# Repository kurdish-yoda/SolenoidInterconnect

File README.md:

# SENSA - Solenoid Interconnect

Genral repository for files pertaining solidnoid interconnect board that is part of SENSA GROUP.  

## Description
The PCB accepts signals comming from 8 solenoids at once and outputs them at individual pinouts. It acts as a "break" in the cable where it also further outputs all of the inputs. ]

## Features
- Daisy chainable.
- 8 solenoid outputs. 

## Pictures

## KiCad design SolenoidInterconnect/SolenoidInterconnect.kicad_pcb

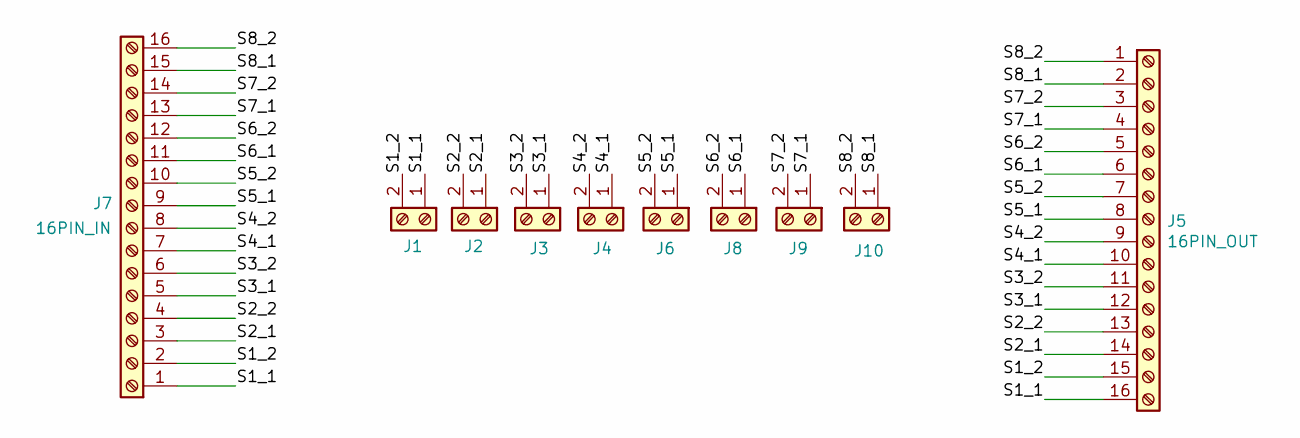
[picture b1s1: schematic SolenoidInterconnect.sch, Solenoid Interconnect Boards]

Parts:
J1, J2, J3, J4, J6, J8, J9, J10: Screw_Terminal_01x02; 2PIN_CH
J5: 16PIN_OUT; 16PIN_CH
J7: 16PIN_IN; 16PIN_CH

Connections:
/S1_1: J1.1, J5.16, J7.1
/S1_2: J1.2, J5.15, J7.2
/S2_1: J2.1, J5.14, J7.3
/S2_2: J2.2, J5.13, J7.4
/S3_1: J3.1, J5.12, J7.5
/S3_2: J3.2, J5.11, J7.6
/S4_1: J4.1, J5.10, J7.7
/S4_2: J4.2, J5.9, J7.8
/S5_1: J5.8, J6.1, J7.9
/S5_2: J5.7, J6.2, J7.10
/S6_1: J5.6, J7.11, J8.1
/S6_2: J5.5, J7.12, J8.2
/S7_1: J5.4, J7.13, J9.1
/S7_2: J5.3, J7.14, J9.2
/S8_1: J5.2, J7.15, J10.1
/S8_2: J5.1, J7.16, J10.2

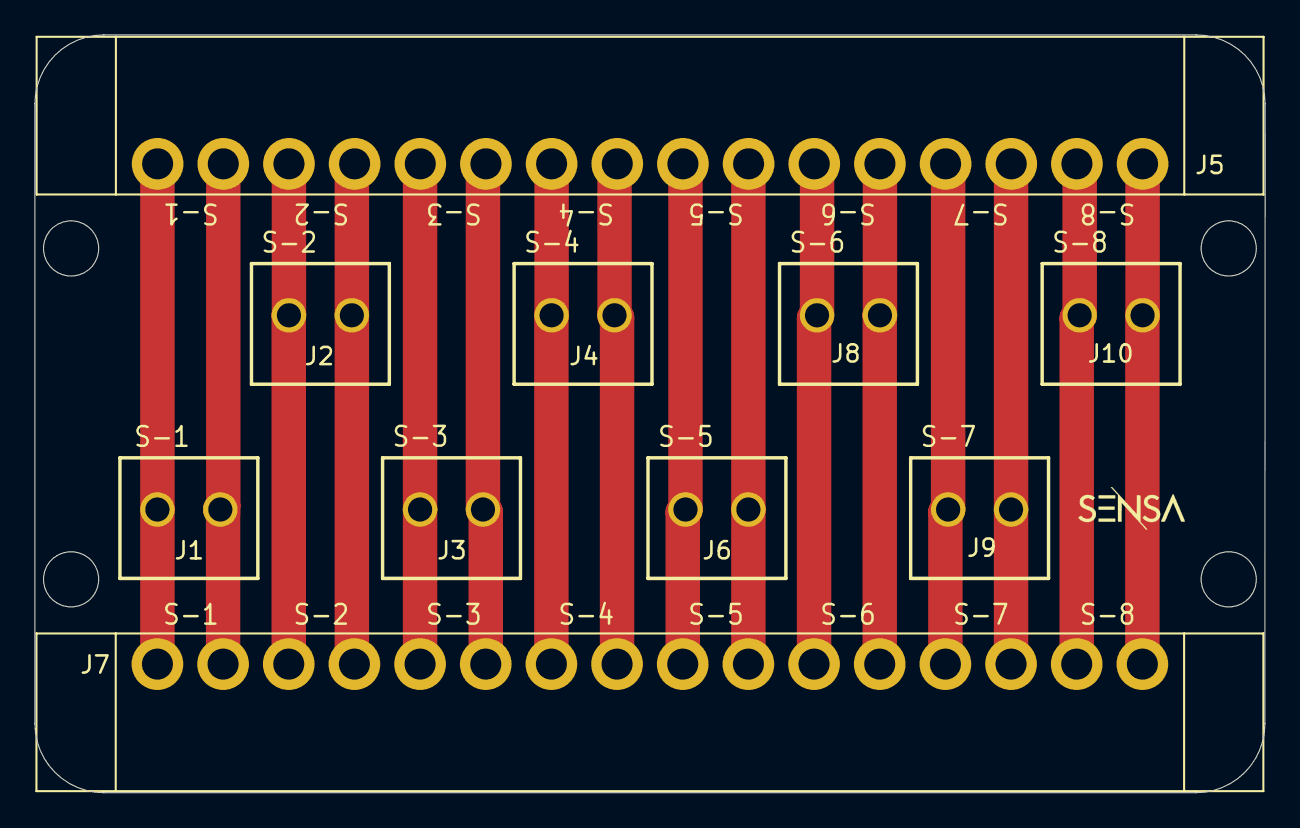
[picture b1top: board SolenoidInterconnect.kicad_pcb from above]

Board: 2 copper layers, 71.4 x 44.0 mm, 10 parts (0 on the bottom side), 16 nets.

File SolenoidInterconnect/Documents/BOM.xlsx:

Item # | *Designator | *Qty | Manufacturer | *Mfg Part # | Description / Value | *Package/Footprint | Type | Your Instructions / Notes | Link
1 | J1, J2, J3, J4, J6, J8, J9, J10 | 8 | JILN | JL15EDGVC-35002G01 | FEMALE CONNECTOR 2POS P = 3.5mm | / | TH |  | https://lcsc.com/product-detail/span-style-background-color-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
2 | J5, J7 | 2 | Ningbo Kangnex Elec | WJ15EDGRM-3.81-16P | FEMALE CONNECTOR 16POS P = 3.81mm | / | TH |  | https://lcsc.com/product-detail/Pluggable-System-Terminal-Bl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
3 | / | 8 | JILN | JL15EDGK-35002G01 | MALE CONNECTOR 2POS P = 3.5mm | / | / | DO NOT PLACE, ONLY INCLUDE | https://lcsc.com/product-detail/Pluggable-System-Terminal-Bl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
4 | / | 2 | Ningbo Kangnex Elec | WJ15EDGKB-3.81-16P | MALE CONNECTOR 16POS P = 3.81mm | / | / | DO NOT PLACE, ONLY INCLUDE | https://lcsc.com/product-detail/Pluggable-span-style-backgro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

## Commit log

2021-10-02 Kicad initialized
2021-10-02 Schematic V1
2021-10-06 V1.0
2021-10-12 Added mounting points
